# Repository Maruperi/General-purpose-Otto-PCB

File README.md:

# General-purpose-Otto-PCB
This project consists on a PCB that can be used in every open source [Otto](https://www.printables.com/model/31955-otto-diy-build-your-own-robot?lang=es) model.

---
⚠️ **WARNING: WORK IN PROGRESS** ⚠️

This project is still under active development.  
Schematics and PCB layout may contain errors and are subject to change.  
**I do not recomend manufacturing any boards based on this design yet.**
---

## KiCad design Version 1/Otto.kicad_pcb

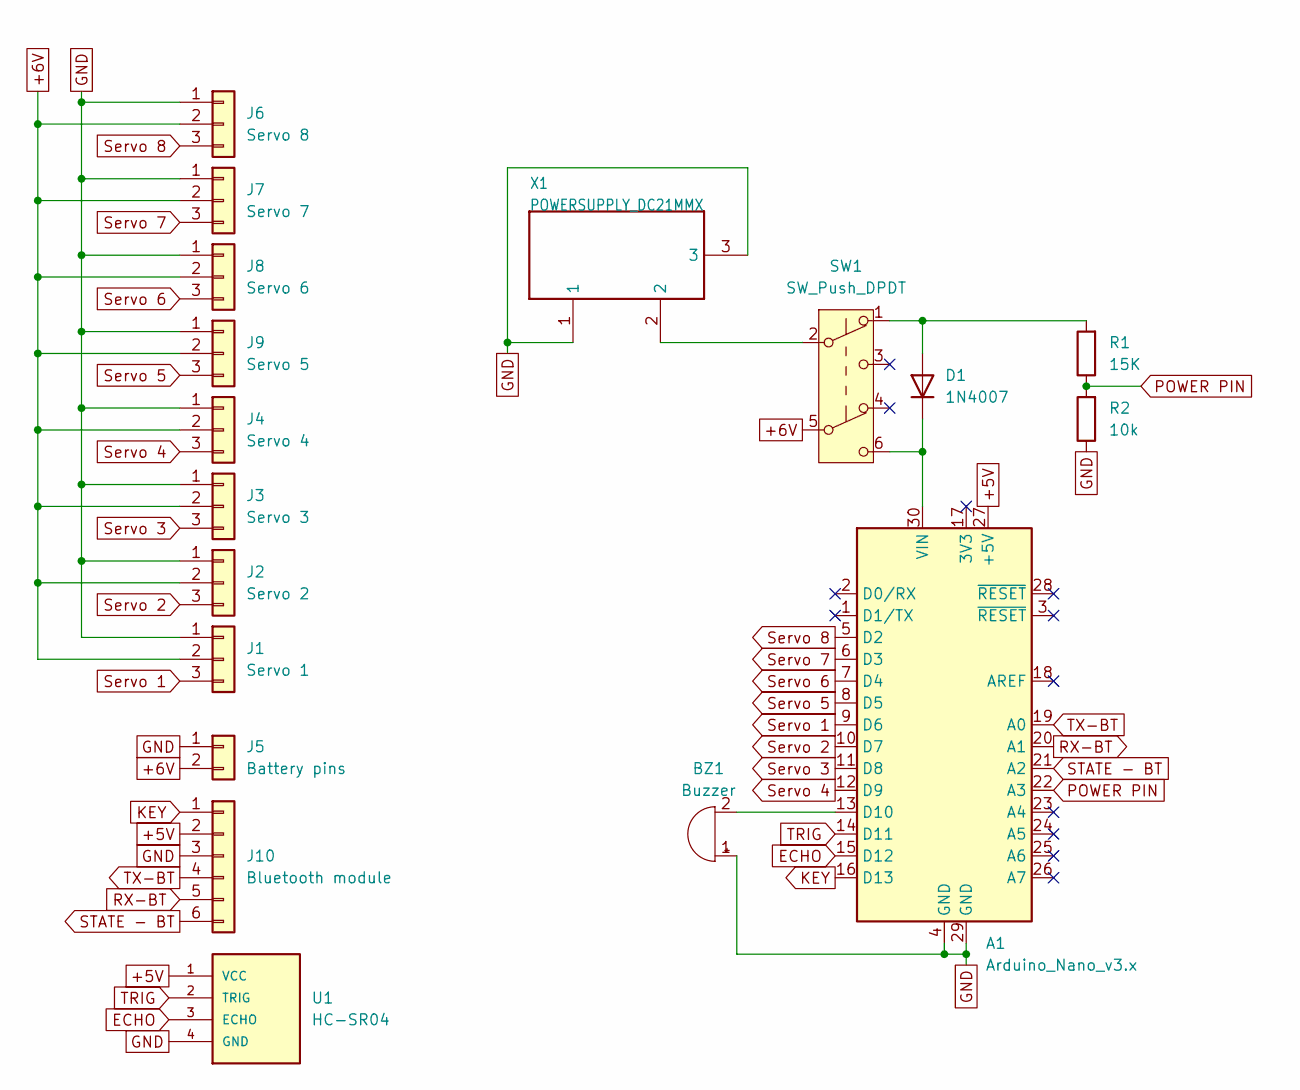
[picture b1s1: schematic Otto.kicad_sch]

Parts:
A1: Arduino_Nano_v3.x; Arduino_Nano
BZ1: Buzzer; Buzzer_12x9.5RM7.6
D1: 1N4007; D_DO-41_SOD81_P10.16mm_Horizontal
J1: Servo 1; PinHeader_1x03_P2.54mm_Vertical
J2: Servo 2; PinHeader_1x03_P2.54mm_Vertical
J3: Servo 3; PinHeader_1x03_P2.54mm_Vertical
J4: Servo 4; PinHeader_1x03_P2.54mm_Vertical
J5: Battery pins; PinHeader_1x02_P2.54mm_Vertical
J6: Servo 8; PinHeader_1x03_P2.54mm_Vertical
J7: Servo 7; PinHeader_1x03_P2.54mm_Vertical
J8: Servo 6; PinHeader_1x03_P2.54mm_Vertical
J9: Servo 5; PinHeader_1x03_P2.54mm_Vertical
J10: Bluetooth module; PinHeader_1x06_P2.54mm_Vertical
R1: 15K; R_Axial_DIN0207_L6.3mm_D2.5mm_P10.16mm_Horizontal
R2: 10k; R_Axial_DIN0207_L6.3mm_D2.5mm_P10.16mm_Horizontal
SW1: SW_Push_DPDT; SW_Push_2P2T_Toggle_CK_PVA2OAH5xxxxxxV2
U1: HC-SR04; XCVR_HC-SR04
X1: POWERSUPPLY_DC21MMX; POWERSUPPLY_DC-21MM

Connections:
+5V: A1.27 (+5V), J10.2, U1.1 (VCC)
+6V: J1.2, J2.2, J3.2, J4.2, J5.2, J6.2, J7.2, J8.2, J9.2, SW1.5 (B)
ECHO: A1.15 (D12), U1.3 (ECHO)
GND: A1.4 (GND), A1.29 (GND), BZ1.1 (+), J1.1, J2.1, J3.1, J4.1, J5.1, J6.1, J7.1, J8.1, J9.1, J10.3, R2.1, U1.4 (GND), X1.1, X1.3
KEY: A1.16 (D13), J10.1
unnamed: A1.13 (D10), BZ1.2 (-)
unnamed: A1.30 (VIN), D1.1 (K), SW1.6 (C)
unnamed: D1.2 (A), R1.2, SW1.1 (A)
unnamed: SW1.2 (B), X1.2
POWER PIN: A1.22 (A3), R1.1, R2.2
RX-BT: A1.20 (A1), J10.5
STATE - BT: A1.21 (A2), J10.6
Servo 1: A1.9 (D6), J1.3
Servo 2: A1.10 (D7), J2.3
Servo 3: A1.11 (D8), J3.3
Servo 4: A1.12 (D9), J4.3
Servo 5: A1.8 (D5), J9.3
Servo 6: A1.7 (D4), J8.3
Servo 7: A1.6 (D3), J7.3
Servo 8: A1.5 (D2), J6.3
TRIG: A1.14 (D11), U1.2 (TRIG)
TX-BT: A1.19 (A0), J10.4

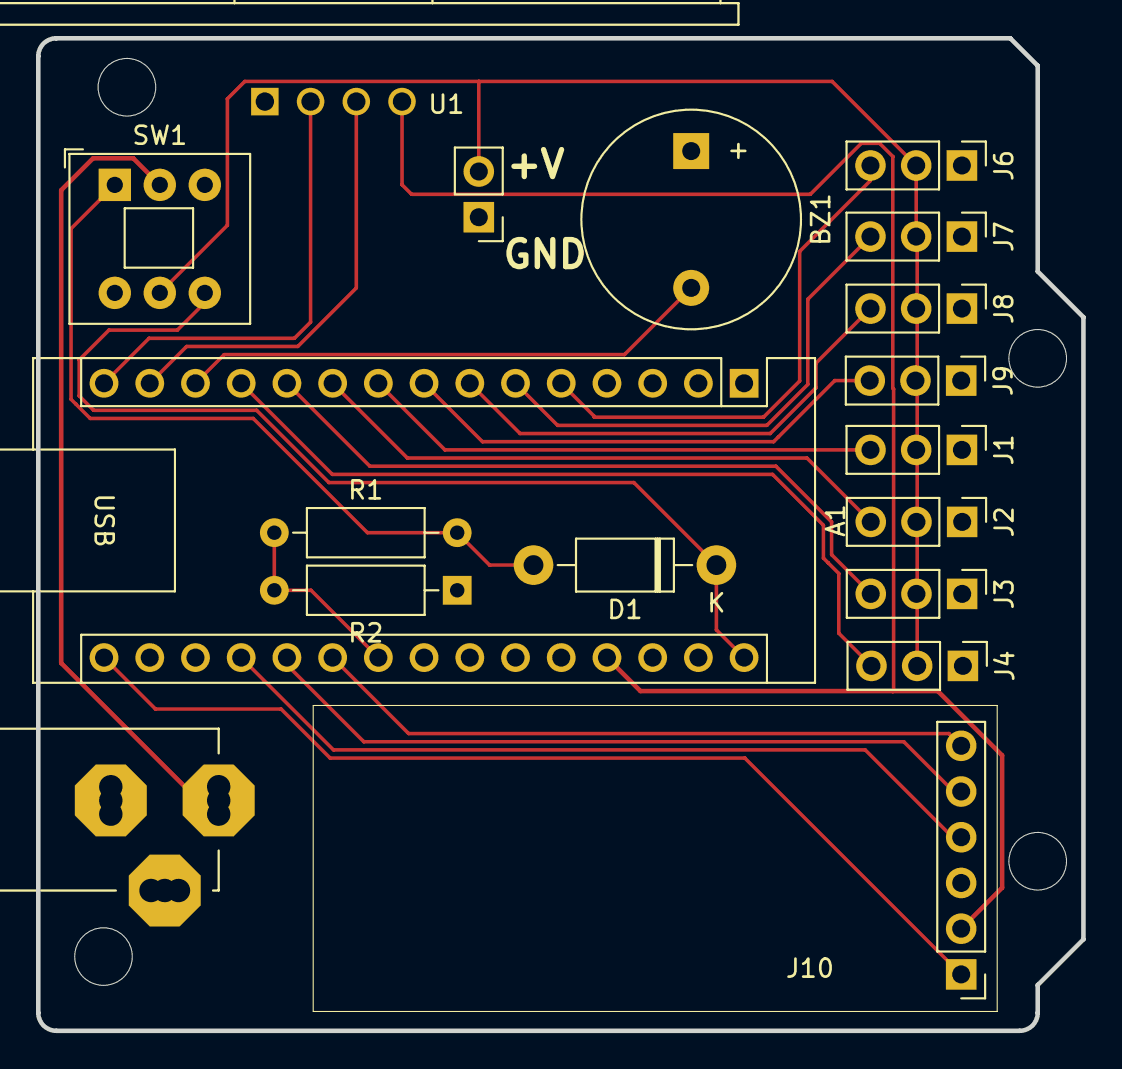
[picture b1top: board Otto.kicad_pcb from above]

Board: 2 copper layers, 58.1 x 55.1 mm, 23 parts (0 on the bottom side), 22 nets.

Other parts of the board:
@HOLE0, @HOLE1, @HOLE2, @HOLE3: (no value)
U$1: DISCLAIMER

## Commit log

2025-05-25 Add general information document
2025-06-23 Create DELETEME
    Added "Version 1" folder
2025-06-23 Create DELETEME
2025-06-23 Added version 1 Otto files
    This version includes:
    - Power jack port / pins for battery
    - On/Off switch
    - Bluetooth module
    - Buzzer
    - Ultrasonic sensor
2025-06-23 Update README.md
    Added warning of work in progress
2025-06-28 Create code tests folder
2025-06-28 Added some test codes
    Added:
    - Ultrasonic sensor test code
    - Buzzer test code
2025-07-01 Upload bluetooth test code
2025-07-01 Update ToDo.md
    Warning of reversed pins of the PCB (bluetooth module pins)
2025-07-01 Add servo test code
2025-07-01 Update ToDo.md
    Added:
    - Redisign power button
2025-07-03 Add main code
    Added main code with control by serial port (keyboard)
